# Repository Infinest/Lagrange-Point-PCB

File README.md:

# Lagrange Point PCB in an MMC5 cartridge
This repository contains gerber files for a PCB that allows transplanting your copy of Lagrange Point into an MMC5-type cartridge shell.
The PCB should fit into both the original shells made by Nintendo as well as these [reproduction ones](https://everdrive.me/accessories/shell-for-fami-cartridge.html).

All parts from the original PCB can be directly transferred over to the new PCB.
The only new part required is the CR2025 coin cell holder. The part number for it is `BK-6219-TR`.

The PCB needs to be ordered with a thickness of 1.2mm and the edge connector should optimally be chamfered.

# Images

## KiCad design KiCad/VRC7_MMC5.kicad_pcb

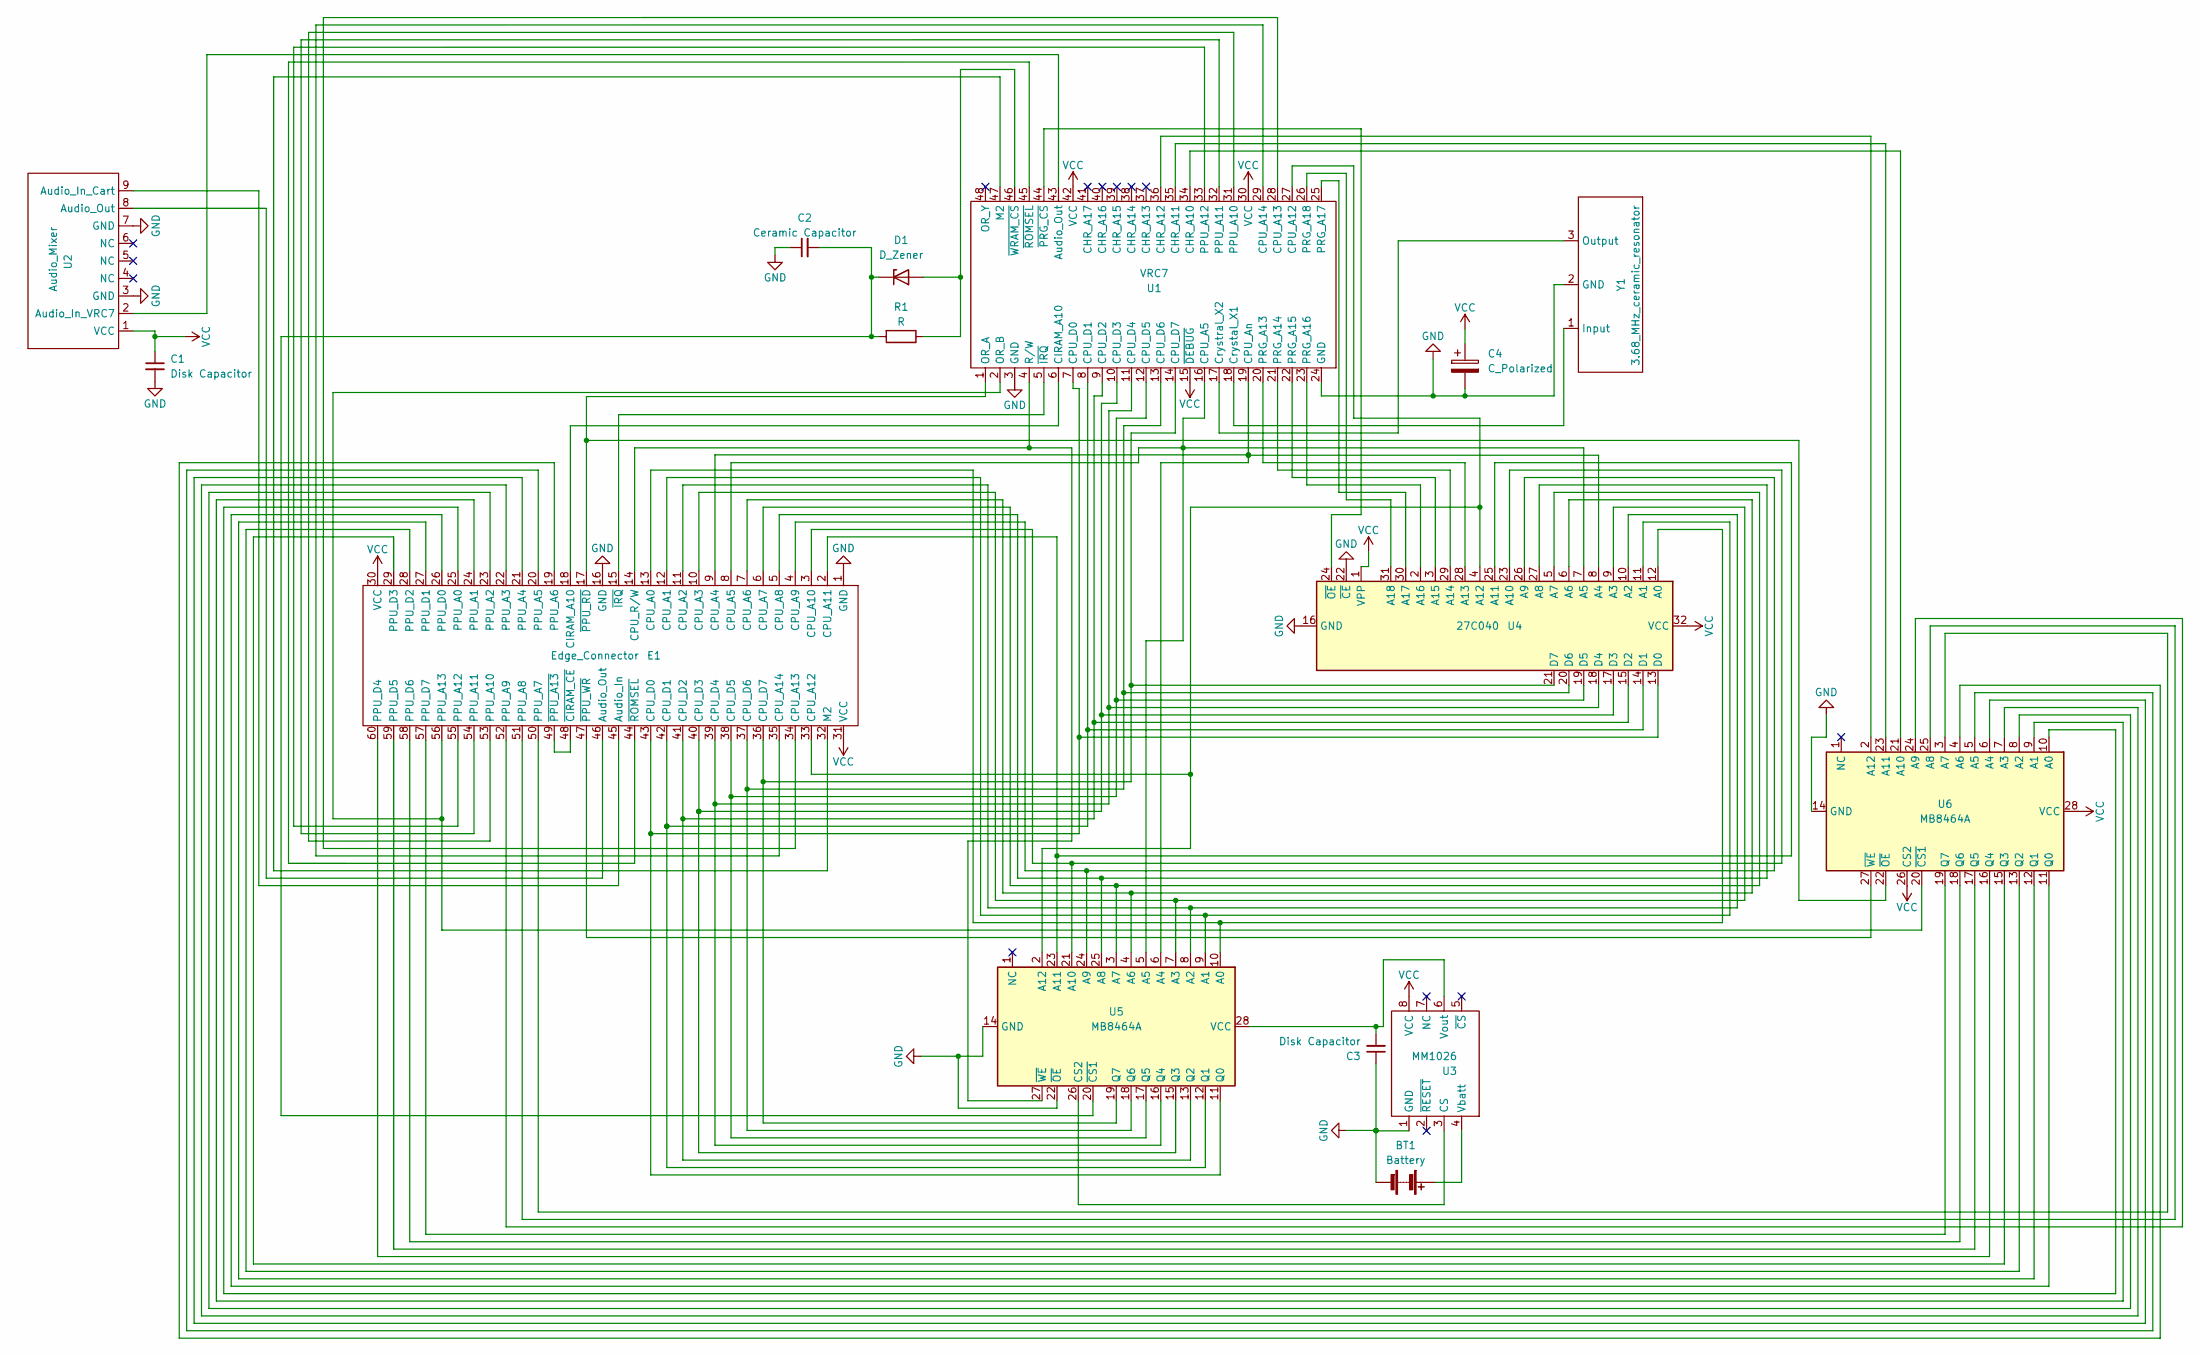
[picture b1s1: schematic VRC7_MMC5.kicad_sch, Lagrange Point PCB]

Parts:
BT1: Battery; BK-6219-TR
C1, C3: Disk Capacitor; C_Disc_D6.0mm_W2.5mm_P5.00mm
C2: Ceramic Capacitor; C_Disc_D3.8mm_W2.6mm_P2.50mm
C4: C_Polarized; C_Radial_D6.3mm_H7.0mm_P2.50mm
D1: D_Zener; D_DO-34_SOD68_P10.16mm_Horizontal
E1: Edge_Connector; Famicom Edge Connector
R1: R; R_Axial_DIN0207_L6.3mm_D2.5mm_P10.16mm_Horizontal
U1: VRC7; DIP-48_W15.24mm_LongPads
U2: Audio_Mixer; Audio Mixer VRC7
U3: MM1026; DIP-8_W7.62mm_LongPads
U4: 27C040; DIP-32_W15.24mm_LongPads
U5, U6: MB8464A; DIP-28_W15.24mm_LongPads
Y1: 3.68_MHz_ceramic_resonator; Resonator-3Pin_W7.0mm_H2.5mm

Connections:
GND: BT1.2 (-), C1.2, C2.1, C3.1, C4.2, E1.1 (GND), E1.16 (GND), U1.3 (GND), U1.24 (GND), U2.3 (GND), U2.7 (GND), U3.1 (GND), U4.16 (GND), U4.22 (~CE), U5.14 (GND), U5.22 (~OE), U6.14 (GND), Y1.2 (GND)
unnamed: BT1.1 (+), U3.4 (Vbatt)
unnamed: C2.2, D1.1 (K), R1.2, U5.20 (~CS1)
unnamed: C3.2, U3.6 (Vout), U5.28 (VCC)
unnamed: D1.2 (A), R1.1, U1.46 (~WRAM_CS)
unnamed: E1.2 (CPU_A11), U4.25 (A11), U5.23 (A11)
unnamed: E1.3 (CPU_A10), U4.23 (A10), U5.21 (A10)
unnamed: E1.4 (CPU_A9), U4.26 (A9), U5.24 (A9)
unnamed: E1.5 (CPU_A8), U4.27 (A8), U5.25 (A8)
unnamed: E1.6 (CPU_A7), U4.5 (A7), U5.3 (A7)
unnamed: E1.7 (CPU_A6), U4.6 (A6), U5.4 (A6)
unnamed: E1.8 (CPU_A5), U1.16 (CPU_A5), U4.7 (A5), U5.5 (A5)
unnamed: E1.9 (CPU_A4), U1.19 (CPU_An), U4.8 (A4), U5.6 (A4)
unnamed: E1.10 (CPU_A3), U4.9 (A3), U5.7 (A3)
unnamed: E1.11 (CPU_A2), U4.10 (A2), U5.8 (A2)
unnamed: E1.12 (CPU_A1), U4.11 (A1), U5.9 (A1)
unnamed: E1.13 (CPU_A0), U4.12 (A0), U5.10 (A0)
unnamed: E1.14 (CPU_R/W), U1.4 (R/W), U5.27 (~WE)
unnamed: E1.15 (~IRQ), U1.5 (~IRQ)
unnamed: E1.17 (~PPU_RD), U1.1 (OR_A), U6.22 (~OE)
unnamed: E1.18 (CIRAM_A10), U1.6 (CIRAM_A10)
unnamed: E1.19 (PPU_A6), U6.4 (A6)
unnamed: E1.20 (PPU_A5), U6.5 (A5)
unnamed: E1.21 (PPU_A4), U6.6 (A4)
unnamed: E1.22 (PPU_A3), U6.7 (A3)
unnamed: E1.23 (PPU_A2), U6.8 (A2)
unnamed: E1.24 (PPU_A1), U6.9 (A1)
unnamed: E1.25 (PPU_A0), U6.10 (A0)
unnamed: E1.26 (PPU_D0), U6.11 (Q0)
unnamed: E1.27 (PPU_D1), U6.12 (Q1)
unnamed: E1.28 (PPU_D2), U6.13 (Q2)
unnamed: E1.29 (PPU_D3), U6.15 (Q3)
unnamed: E1.32 (M2), U1.47 (M2)
unnamed: E1.33 (CPU_A12), U1.27 (CPU_A12), U4.4 (A12), U5.2 (A12)
unnamed: E1.34 (CPU_A13), U1.28 (CPU_A13)
unnamed: E1.35 (CPU_A14), U1.29 (CPU_A14)
unnamed: E1.36 (CPU_D7), U1.14 (CPU_D7), U4.21 (D7), U5.19 (Q7)
unnamed: E1.37 (CPU_D6), U1.13 (CPU_D6), U4.20 (D6), U5.18 (Q6)
unnamed: E1.38 (CPU_D5), U1.12 (CPU_D5), U4.19 (D5), U5.17 (Q5)
unnamed: E1.39 (CPU_D4), U1.11 (CPU_D4), U4.18 (D4), U5.16 (Q4)
unnamed: E1.40 (CPU_D3), U1.10 (CPU_D3), U4.17 (D3), U5.15 (Q3)
unnamed: E1.41 (CPU_D2), U1.9 (CPU_D2), U4.15 (D2), U5.13 (Q2)
unnamed: E1.42 (CPU_D1), U1.8 (CPU_D1), U4.14 (D1), U5.12 (Q1)
unnamed: E1.43 (CPU_D0), U1.7 (CPU_D0), U4.13 (D0), U5.11 (Q0)
unnamed: E1.44 (~ROMSEL), U1.45 (~ROMSEL)
unnamed: E1.45 (Audio_In), U2.9 (Audio_In_Cart)
unnamed: E1.46 (Audio_Out), U2.8 (Audio_Out)
unnamed: E1.47 (~PPU_WR), U6.27 (~WE)
unnamed: E1.48 (~CIRAM_CE), E1.49 (~PPU_A13)
unnamed: E1.50 (PPU_A7), U6.3 (A7)
unnamed: E1.51 (PPU_A8), U6.25 (A8)
unnamed: E1.52 (PPU_A9), U6.24 (A9)
unnamed: E1.53 (PPU_A10), U1.31 (PPU_A10)
unnamed: E1.54 (PPU_A11), U1.32 (PPU_A11)
unnamed: E1.55 (PPU_A12), U1.33 (PPU_A12)
unnamed: E1.56 (PPU_A13), U1.2 (OR_B), U6.20 (~CS1)
unnamed: E1.57 (PPU_D7), U6.19 (Q7)
unnamed: E1.58 (PPU_D6), U6.18 (Q6)
unnamed: E1.59 (PPU_D5), U6.17 (Q5)
unnamed: E1.60 (PPU_D4), U6.16 (Q4)
unnamed: U1.17 (Crystral_X2), Y1.3 (Output)
unnamed: U1.18 (Crystal_X1), Y1.1 (Input)
unnamed: U1.20 (PRG_A13), U4.28 (A13)
unnamed: U1.21 (PRG_A14), U4.29 (A14)
unnamed: U1.22 (PRG_A15), U4.3 (A15)
unnamed: U1.23 (PRG_A16), U4.2 (A16)
unnamed: U1.25 (PRG_A17), U4.30 (A17)
unnamed: U1.26 (PRG_A18), U4.31 (A18)
unnamed: U1.34 (CHR_A10), U6.21 (A10)
unnamed: U1.35 (CHR_A11), U6.23 (A11)
unnamed: U1.36 (CHR_A12), U6.2 (A12)
unnamed: U1.43 (Audio_Out), U2.2 (Audio_In_VRC7)
unnamed: U1.44 (~PRG_CS), U4.24 (~OE)
unnamed: U3.3 (CS), U5.26 (CS2)
VCC: C1.1, C4.1, E1.30 (VCC), E1.31 (VCC), U1.15 (~DEBUG), U1.30 (VCC), U1.42 (VCC), U2.1 (VCC), U3.8 (VCC), U4.1 (VPP), U4.32 (VCC), U6.26 (CS2), U6.28 (VCC)

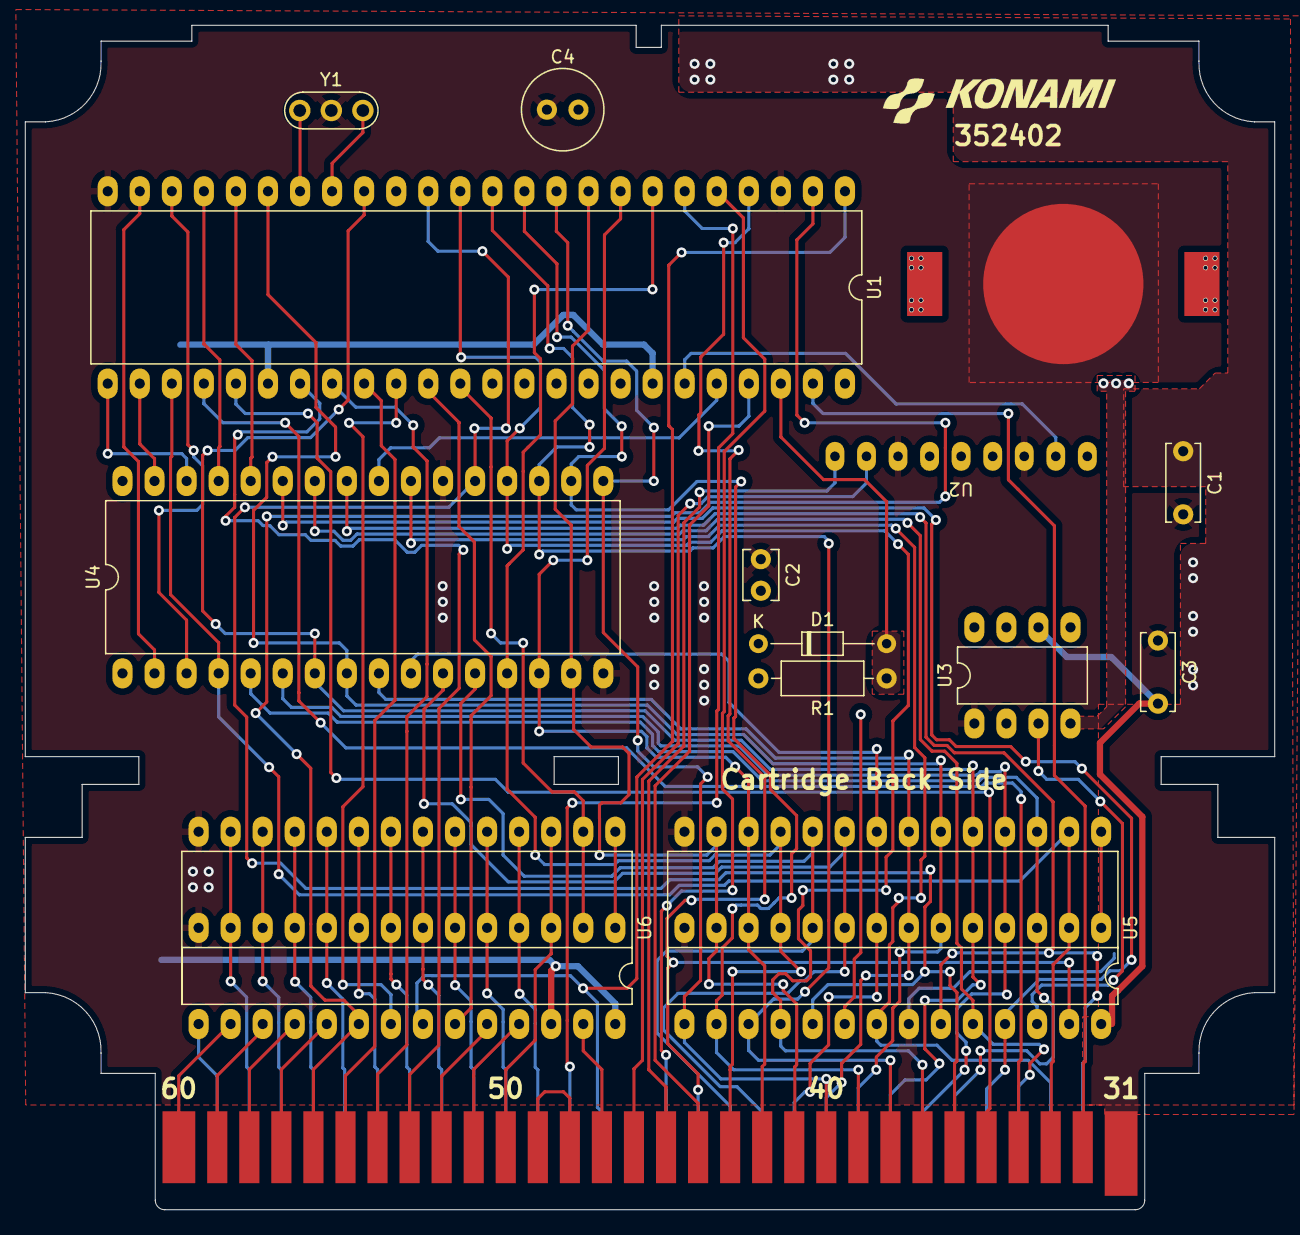
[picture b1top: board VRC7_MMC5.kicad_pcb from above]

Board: 2 copper layers, 99.0 x 93.8 mm, 15 parts (0 on the bottom side), 75 nets.

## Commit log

2023-05-03 Add gerber files
2023-09-23 Add KiCad project folder
2023-09-23 Rename folder
